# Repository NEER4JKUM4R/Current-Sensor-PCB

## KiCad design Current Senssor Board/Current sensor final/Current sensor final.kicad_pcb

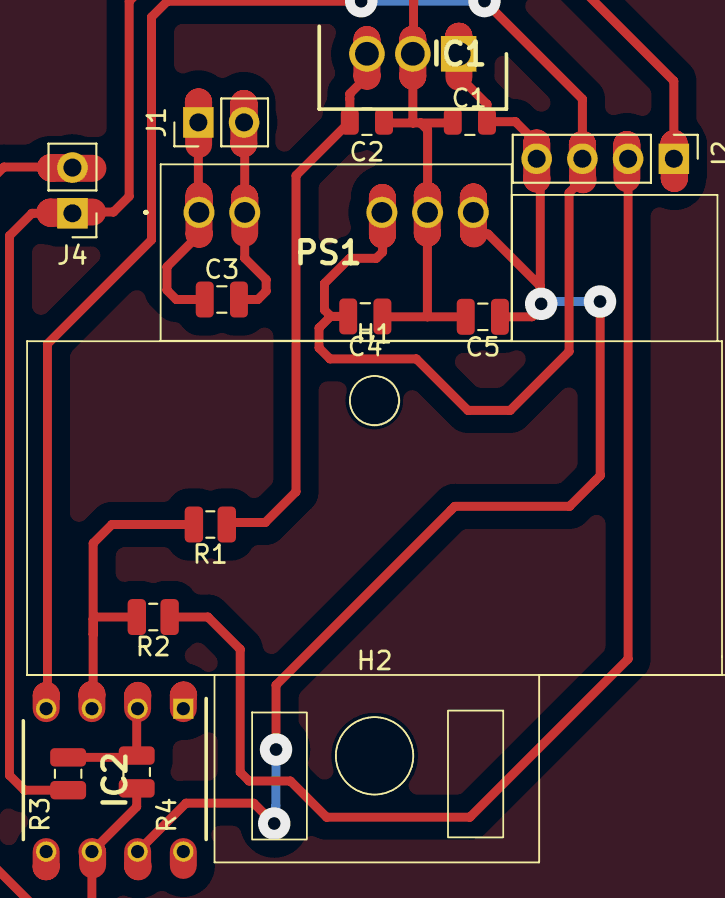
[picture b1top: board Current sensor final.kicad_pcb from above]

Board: 2 copper layers, 18 parts (0 on the bottom side), 10 nets.

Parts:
C1: .33 uf; C_0805_2012Metric
C2: .01 uf; C_0805_2012Metric
C3: 100 nf; C_0805_2012Metric
C4, C5: 470 nf; C_0805_2012Metric
H1: MountingHole; MountingHole_2.7mm
H2: MountingHole; MountingHole_4.3mm_M4
IC1: L7805CV; TO255P460X1020X2008-3P
IC2: OP07CP; DIP794W53P254L959H508Q8N
J1: input 2; PinHeader_1x02_P2.54mm_Vertical
J2: Conn_01x04_Pin; PinHeader_1x04_P2.54mm_Vertical
J4: output; PinHeader_1x02_P2.54mm_Vertical
PS1: MGJ2D151505SC
R1, R2, R3, R4: 1k; R_0805_2012Metric
U1: current sensor footprint

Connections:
0: C1.1, C2.1, C4.1, C5.2, IC1.2 (GROUND), J2.1, J4.1, PS1.6 (OV), R3.2
+5: C3.1, J1.1, PS1.1 (+VIN)
+15: C1.2, C5.1, IC1.1 (INPUT), IC2.7 (VCC+), J2.4, PS1.7 (+VOUT)
+-4 V: J2.2, R2.1
-15: C4.2, IC2.4 (VCC-), J2.3, PS1.5 (-VOUT)
unnamed: C2.2, IC1.3 (OUTPUT), R1.1
unnamed: IC2.3 (IN+), R1.2, R2.2
unnamed: IC2.2 (IN-), R3.1, R4.1
unnamed: IC2.6 (OUT), J4.2, R4.2
gnd: C3.2, J1.2, PS1.2 (-VIN)

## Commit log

2023-07-23 First files
2023-07-23 voltage regulator datasheet added
